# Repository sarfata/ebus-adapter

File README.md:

# eBus Adapter

This is a read/write adapter for eBus heating bus. It can be connected to a
USB-serial adapter (3.3V or 5V) - or to a Particle Photon.

## Software

Coming soon!

## Links

 * [Inspiration for this design](https://www.mikrocontroller.net/topic/346833)
 * [And also](https://wiki.fhem.de/wiki/EBUS#Platine)
 * [Check out the ebusd hardware wiki
   page](https://github.com/john30/ebusd/wiki/6.-Hardware)

## License

CC-BY-SA

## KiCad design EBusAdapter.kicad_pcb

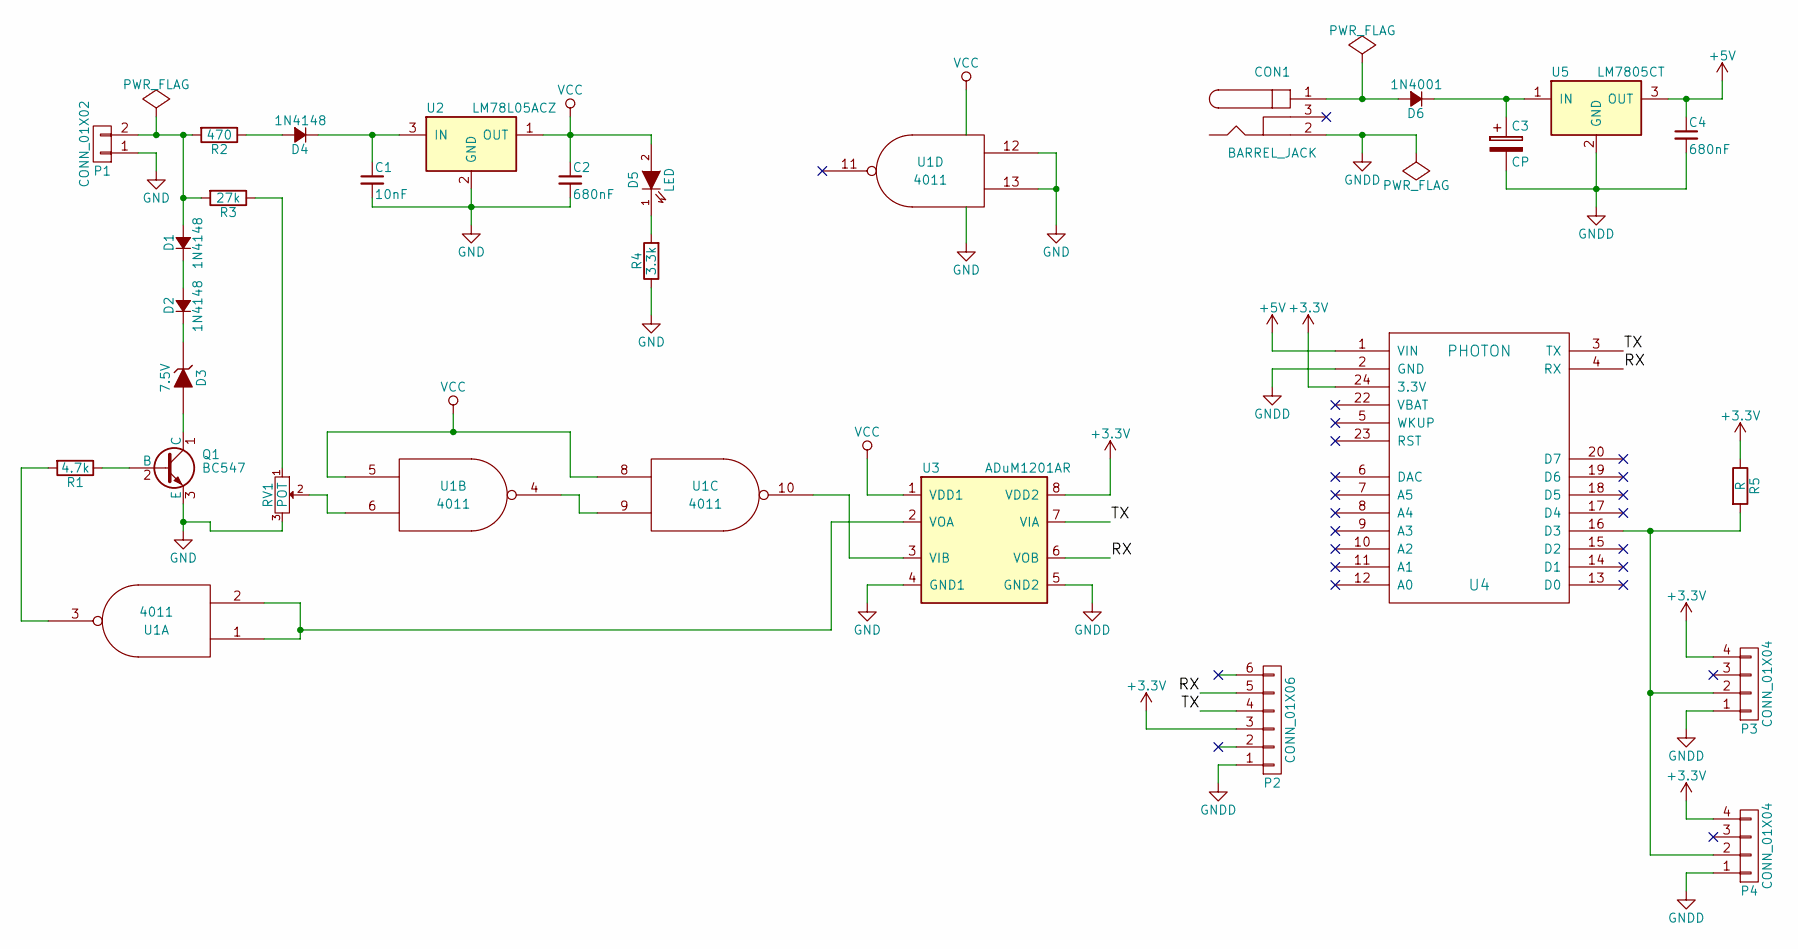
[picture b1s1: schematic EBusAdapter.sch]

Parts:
C1: 10nF; C_Disc_D6_P5
C2, C4: 680nF; C_Disc_D6_P5
C3: CP; C_Radial_D8_L11.5_P3.5
CON1: BARREL_JACK
D1, D2, D4: 1N4148; Diode_DO-35_SOD27_Horizontal_RM10
D3: 7.5V; Diode_DO-35_SOD27_Horizontal_RM10
D5: LED; LED-5MM
D6: 1N4001; Diode_DO-35_SOD27_Horizontal_RM10
P1: CONN_01X02; PhoenixContact_MC-G_02x5.08mm_Angled
P2: CONN_01X06; Socket_Strip_Straight_1x06
P3, P4: CONN_01X04; Molex_KK-6410-04_04x2.54mm_Straight
Q1: BC547; TO-92_Inline_Wide
R1: 4.7k; Resistor_Horizontal_RM10mm
R2: 470; Resistor_Horizontal_RM10mm
R3: 27k; Resistor_Horizontal_RM10mm
R4: 3.3k; Resistor_Horizontal_RM10mm
R5: R; Resistor_Horizontal_RM10mm
RV1: POT; TRIMMER_5_10
U1: 4011; DIP-14_W7.62mm_LongPads
U2: LM78L05ACZ; TO-92_Inline_Wide
U3: ADuM1201AR; SOIC-8_3.9x4.9mm_Pitch1.27mm
U4: PHOTON
U5: LM7805CT; TO-220_Neutral123_Horizontal_LargePads

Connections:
+3V3: P2.3, P3.4, P4.4, R5.1, U3.8 (VDD2), U4.24 (3.3V)
+5V: C4.1, U4.1 (VIN), U5.3 (OUT)
/RX: P2.5, U3.6 (VOB), U4.4 (RX)
/TX: P2.4, U3.7 (VIA), U4.3 (TX)
GND: C1.2, C2.2, P1.1, Q1.3 (E), R4.1, RV1.3, U1.7 (VSS), U1.12, U1.13, U2.2 (GND), U3.4 (GND1)
GNDD: C3.2, C4.2, CON1.2, P2.1, P3.1, P4.1, U3.5 (GND2), U4.2 (GND), U5.2 (GND)
unnamed: C1.1, D4.1 (K), U2.3 (IN)
unnamed: C3.1, D6.1 (K), U5.1 (IN)
unnamed: CON1.1, D6.2 (A)
unnamed: D1.1 (K), D2.2 (A)
unnamed: D1.2 (A), P1.2, R2.2, R3.2
unnamed: D2.1 (K), D3.1 (K)
unnamed: D3.2 (A), Q1.1 (C)
unnamed: D4.2 (A), R2.1
unnamed: D5.1 (K), R4.2
unnamed: P3.2, P4.2, R5.2, U4.16 (D3)
unnamed: Q1.2 (B), R1.1
unnamed: R1.2, U1.3
unnamed: R3.1, RV1.1
unnamed: RV1.2, U1.6
unnamed: U1.1, U1.2, U3.2 (VOA)
unnamed: U1.4, U1.9
unnamed: U1.10, U3.3 (VIB)
VCC: C2.1, D5.2 (A), U1.5, U1.8, U1.14 (VDD), U2.1 (OUT), U3.1 (VDD1)

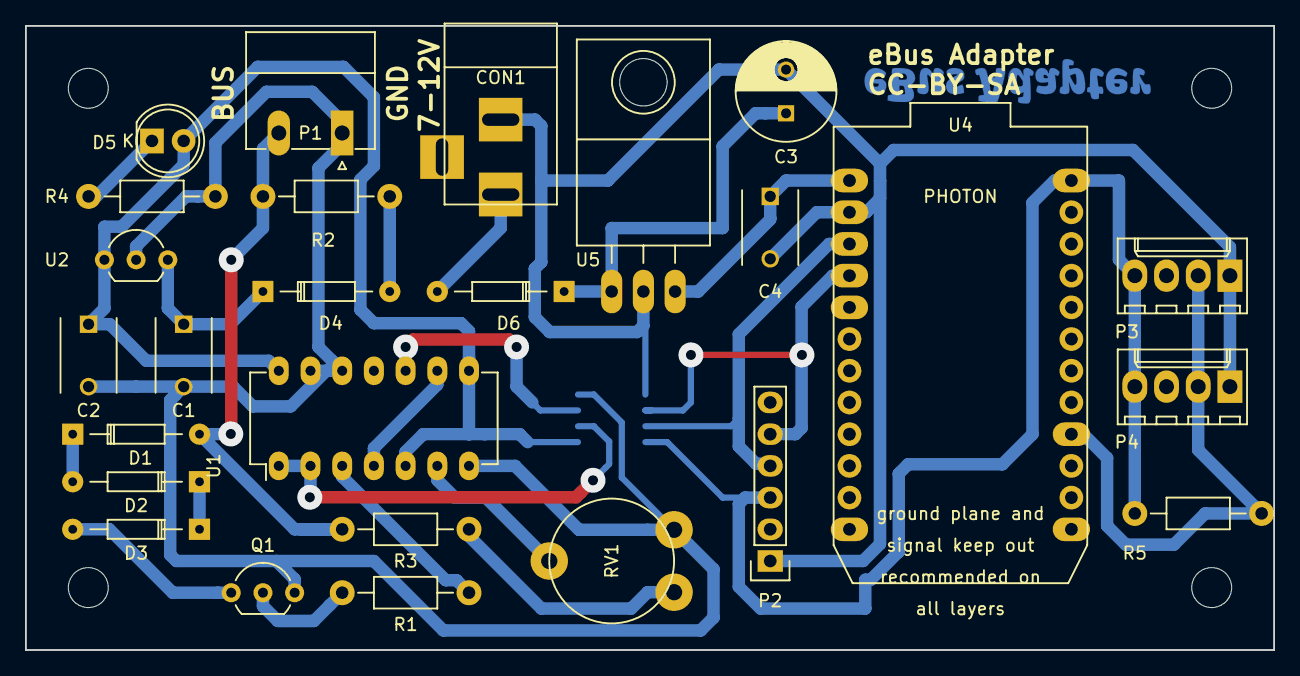
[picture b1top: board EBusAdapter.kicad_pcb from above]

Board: 2 copper layers, 100.0 x 50.0 mm, 27 parts (1 on the bottom side), 24 nets.

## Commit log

2016-12-12 schematic wip
2016-12-14 Initial hardware
2016-12-16 Fix CD4011 power supply (was inverted) - added logo
2016-12-16 Add gitignore
